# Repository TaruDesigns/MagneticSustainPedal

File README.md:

# MagneticSustainPedal
## Repairs for the F-30 pedal in the VPC1 and other keyboards
The F-30 pedal by Fatar is a 3  pedal unit included in some high end MIDI keyboards, with the Kawai VPC1 being a popular one. This pedal tends to fail after a while so I compiled all the repairs/upgrades onto this repository. The PDFs explains all of these upgrades.

### Magnetic sensor
One of the fixes involves making a custom circuit for one of the pedals. The files for this circuit are to be used with EAGLE, but I've also included the CAM Job so you can order the PCB online.

### Updates

I'm happy with my fix, however, if you try any of the other fixes, feel free to contact me and I will add it to the repo

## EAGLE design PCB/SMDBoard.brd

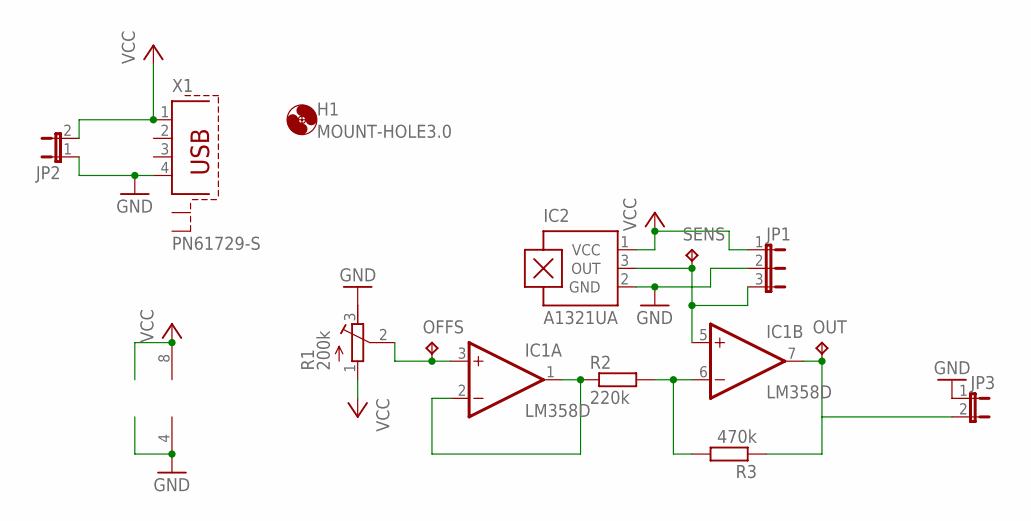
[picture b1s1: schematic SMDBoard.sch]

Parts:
H1: MOUNT-HOLE3.0; 3,0
IC1: LM358D; SO08
IC2: A1321UA; SIP3-UA
JP1: JP2E; JP2
JP2, JP3: JP1E; JP1
OFFS: TPB1,27; B1,27
OUT: TPB1,27; B1,27
R1: 200k; RTRIM3296W
R2: 220k; R0805
R3: 470k; R0805
SENS: TPB1,27; B1,27
X1: PN61729-S

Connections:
GND: IC1.4 (V-), IC2.2 (GND), JP1.2, JP2.1, JP3.1, R1.3 (E), X1.4
unnamed: IC1.1 (OUT), IC1.2 (-IN), R2.1
unnamed: IC1.6 (-IN), R2.2, R3.2
unnamed: IC1.7 (OUT), JP3.2, OUT.TP, R3.1
unnamed: IC1.5 (+IN), IC2.3 (OUT), JP1.3, SENS.TP
OFFS: IC1.3 (+IN), OFFS.TP, R1.2 (S)
VCC: IC1.8 (V+), IC2.1 (VCC), JP1.1, JP2.2, R1.1 (A), X1.1

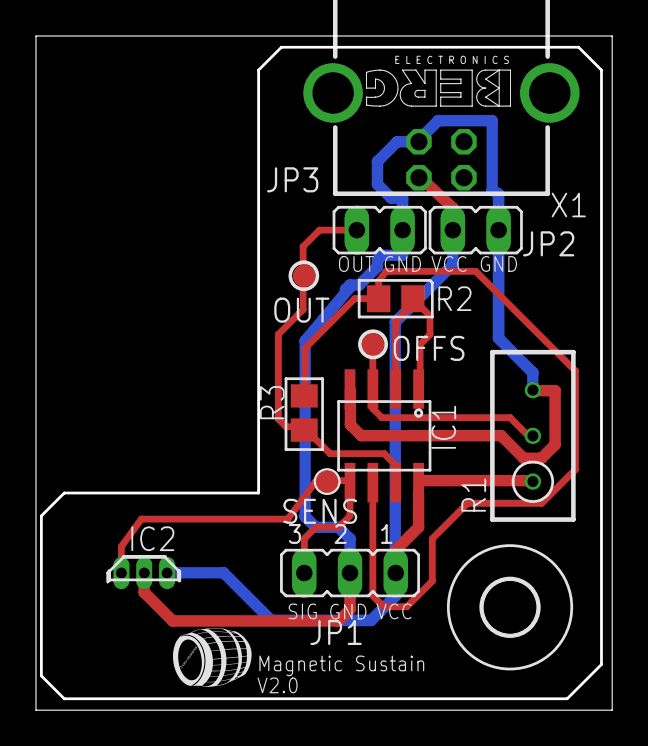
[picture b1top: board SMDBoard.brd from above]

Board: 2 copper layers, 31.9 x 37.3 mm, 13 parts (0 on the bottom side), 7 nets.

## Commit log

2021-06-29 Added PCB and Descriptions
    Added EAGLE Files, MICROCAP Simulation files as well as descriptions in PDF format.
